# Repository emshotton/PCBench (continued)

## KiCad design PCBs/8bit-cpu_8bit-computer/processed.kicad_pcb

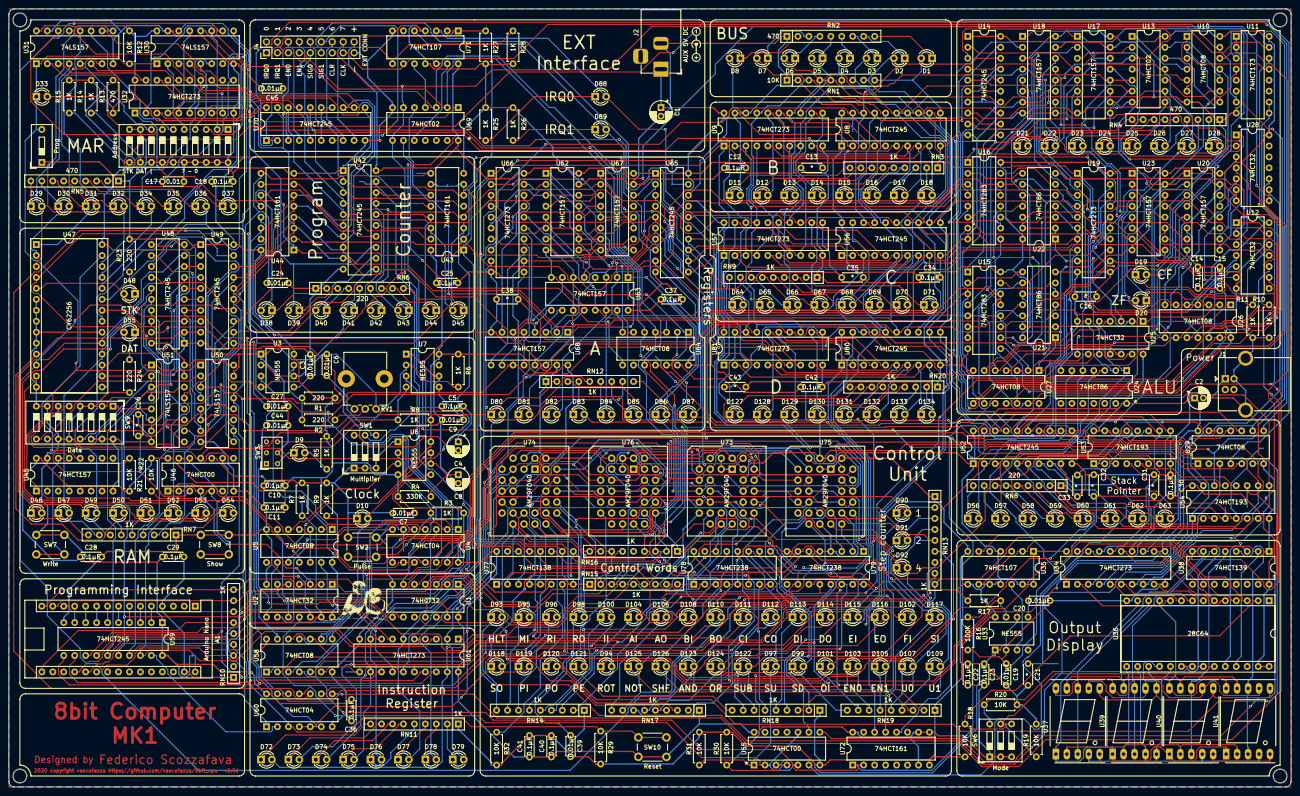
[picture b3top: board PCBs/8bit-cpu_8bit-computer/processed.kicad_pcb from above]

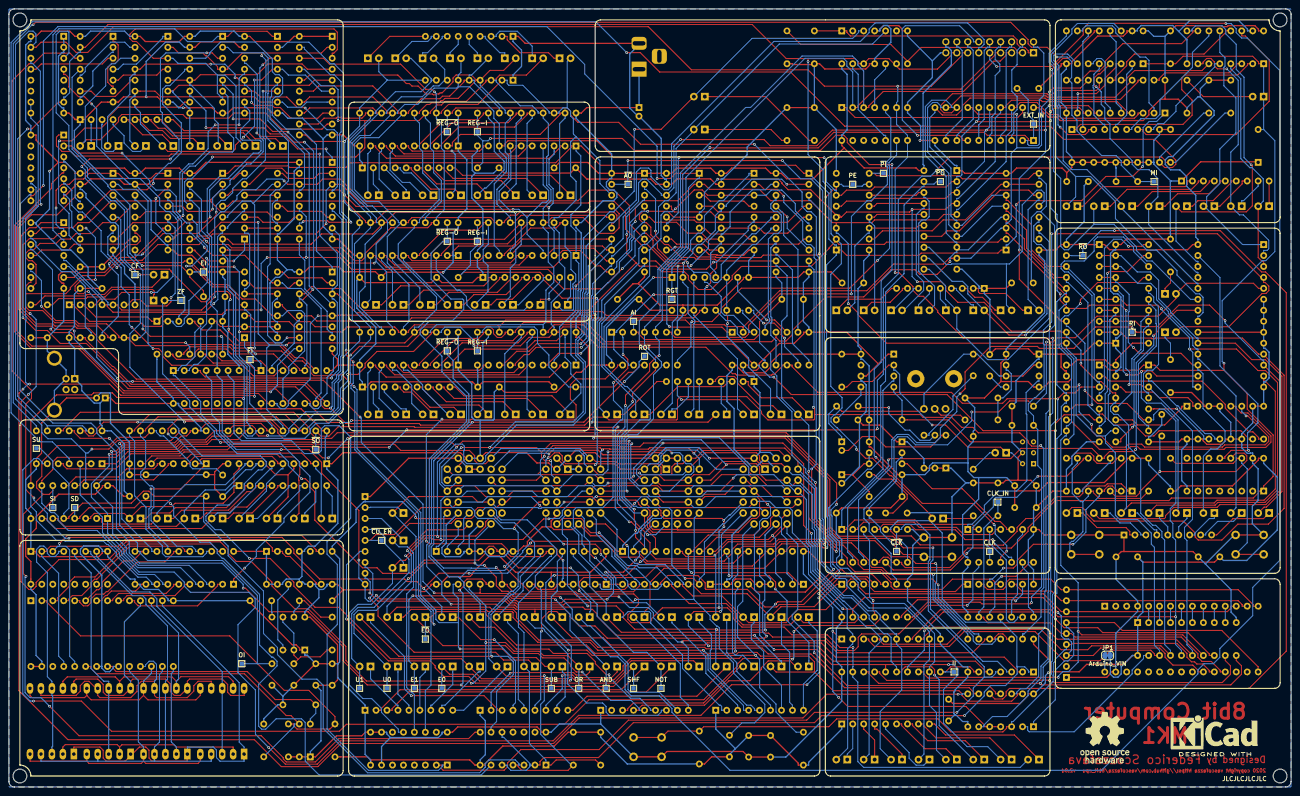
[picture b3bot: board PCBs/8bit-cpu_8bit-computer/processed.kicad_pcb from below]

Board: 2 copper layers, 297.2 x 180.3 mm, 377 parts (44 on the bottom side), 516 nets.

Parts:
A1: Arduino Nano; Arduino_Nano
C1, C2: 10µF; CP_Radial_D5.0mm_P2.00mm
C3, C6, C7, C9, C19, C20, C39, C45: 0.01µF; C_Disc_D4.3mm_W1.9mm_P5.00mm
C4, C8: 1µF; CP_Radial_D5.0mm_P2.00mm
C5, C10, C11, C12, C14, C15, C18, C22, C23, C25, C28, C29, C30, C34, C36, C37, C40, C41, C42: 0.1µF; C_Disc_D4.3mm_W1.9mm_P5.00mm
C13, C16, C21, C26, C31, C32, C33, C35, C38, C43: *; C_Disc_D4.3mm_W1.9mm_P5.00mm
C17: 0.01; C_Disc_D4.3mm_W1.9mm_P5.00mm
C24, C27, C44: 0.01µf; C_Disc_D4.3mm_W1.9mm_P5.00mm
D1, D2, D3, D4, D5, D6, D7, D8, D21, D22, D23, D24, D25, D26, D27, D28, D29, D30, D31, D32, D33, D34, D35, D36, D37: RED; LED_D3.0mm
D9, D11, D12, D13, D14, D15, D16, D17, D18, D46, D47, D49, D50, D51, D52, D53, D54, D64, D65, D66, D67, D68, D69, D70, D71, D80, D81, D82, D83, D84, D85, D86, D87, D127, D128, D129, D130, D131, D132, D133, D134: GREEN; LED_D3.0mm
D10, D72, D73, D74, D75, D76, D77, D78, D79, D93, D94, D95, D96, D97, D98, D99, D100, D101, D102, D103, D104, D105, D106, D107, D108, D109, D110, D111, D112, D113, D114, D115, D116, D117, D118, D119, D120, D121, D122, D123, D124, D125, D126: BLUE; LED_D3.0mm
D19, D20, D88, D89: WHITE; LED_D3.0mm
D38, D39, D40, D41, D42, D43, D44, D45, D48, D55, D56, D57, D58, D59, D60, D61, D62, D63, D90, D91, D92: YELLOW; LED_D3.0mm
G0: LOGO; parrot
G1: Symbol_Barrel_Polarity
G2: KiCad-Logo2_8mm_SilkScreen
G3: OSHW-Logo_11.4x12mm_SilkScreen
J1: USB_B-8bit-computer-rescue; USB_B_OST_USB-B1HSxx_Horizontal
J2: Barrel_Jack_Switch; BarrelJack_Horizontal
J4: EXT-CONN; PinHeader_2x09_P2.54mm_Vertical
JP1: Arduino_VIN; SolderJumper-2_P1.3mm_Bridged_RoundedPad1.0x1.5mm
MH0, MH1, MH2, MH3: MountingHole_3.2mm_M3
R1, R2, R23, R24: 220; R_Axial_DIN0207_L6.3mm_D2.5mm_P7.62mm_Horizontal
R3, R5, R6, R7, R8, R9, R10, R11, R14, R15, R17, R25, R26, R27, R28: 1K; R_Axial_DIN0207_L6.3mm_D2.5mm_P7.62mm_Horizontal
R4: 330K; R_Axial_DIN0207_L6.3mm_D2.5mm_P7.62mm_Horizontal
R12, R18, R19, R20, R21, R22, R29, R30, R31, R32: 10K; R_Axial_DIN0207_L6.3mm_D2.5mm_P7.62mm_Horizontal
R13: 470; R_Axial_DIN0207_L6.3mm_D2.5mm_P7.62mm_Horizontal
R16: 100K; R_Axial_DIN0207_L6.3mm_D2.5mm_P7.62mm_Horizontal
RN1: 10K; R_Array_SIP9
RN2, RN4, RN5: 470; R_Array_SIP9
RN3, RN7, RN9, RN10, RN11, RN12, RN13, RN14, RN15, RN16, RN17, RN18, RN19, RN20: 1K; R_Array_SIP9
RN6, RN8: 220; R_Array_SIP9
RV1: 1M; Potentiometer_Bourns_PTV09A-1_Single_Vertical
SW1: Multiplier; SW_DIP_SPSTx03_Slide_9.78x9.8mm_W7.62mm_P2.54mm
SW2: Pulse; SW_PUSH_6mm_H5mm
SW3: Manual; SW_NKK_GW12LJP
SW4: Prog; SW_DIP_SPSTx01_Slide_9.78x4.72mm_W7.62mm_P2.54mm
SW5: Address; SW_DIP_SPSTx10_Slide_9.78x27.58mm_W7.62mm_P2.54mm
SW6: Mode; SW_DIP_SPSTx03_Slide_9.78x9.8mm_W7.62mm_P2.54mm
SW7: Write; SW_PUSH_6mm_H5mm
SW8: Show; SW_PUSH_6mm_H5mm
SW9: Data; SW_DIP_SPSTx08_Slide_9.78x22.5mm_W7.62mm_P2.54mm
SW10: Reset; SW_PUSH_6mm_H5mm
TP1: CLK_IN; TestPoint_Pad_1.0x1.0mm
TP2: CLK; TestPoint_Pad_1.0x1.0mm
TP3: ~CLK; TestPoint_Pad_1.0x1.0mm
TP4, TP26, TP40: ~REG-O; TestPoint_Pad_1.0x1.0mm
TP5, TP27, TP41: REG-I; TestPoint_Pad_1.0x1.0mm
TP6: ~FI; TestPoint_Pad_1.0x1.0mm
TP7: ZF; TestPoint_Pad_1.0x1.0mm
TP8: CF; TestPoint_Pad_1.0x1.0mm
TP9: OR; TestPoint_Pad_1.0x1.0mm
TP10: AND; TestPoint_Pad_1.0x1.0mm
TP11: EI; TestPoint_Pad_1.0x1.0mm
TP12: ~EO; TestPoint_Pad_1.0x1.0mm
TP13: NOT; TestPoint_Pad_1.0x1.0mm
TP14: SUB; TestPoint_Pad_1.0x1.0mm
TP15: MI; TestPoint_Pad_1.0x1.0mm
TP16: OI; TestPoint_Pad_1.0x1.0mm
TP17: ~PO; TestPoint_Pad_1.0x1.0mm
TP18: PE; TestPoint_Pad_1.0x1.0mm
TP19: ~PI; TestPoint_Pad_1.0x1.0mm
TP20: ~RO; TestPoint_Pad_1.0x1.0mm
TP21: RI; TestPoint_Pad_1.0x1.0mm
TP22: ~SO; TestPoint_Pad_1.0x1.0mm
TP23: SU; TestPoint_Pad_1.0x1.0mm
TP24: SD; TestPoint_Pad_1.0x1.0mm
TP25: SI; TestPoint_Pad_1.0x1.0mm
TP28: II; TestPoint_Pad_1.0x1.0mm
TP29: AI; TestPoint_Pad_1.0x1.0mm
TP30: ~AO; TestPoint_Pad_1.0x1.0mm
TP31: RGT; TestPoint_Pad_1.0x1.0mm
TP32: ROT; TestPoint_Pad_1.0x1.0mm
TP33: SHF; TestPoint_Pad_1.0x1.0mm
TP34: E0; TestPoint_Pad_1.0x1.0mm
TP35: EXT_IN; TestPoint_Pad_1.0x1.0mm
TP36: E1; TestPoint_Pad_1.0x1.0mm
TP37: U0; TestPoint_Pad_1.0x1.0mm
TP38: U1; TestPoint_Pad_1.0x1.0mm
TP39: ~CU_EN; TestPoint_Pad_1.0x1.0mm
U1, U2, U12, U25, U28: 74HCT32; DIP-14_W7.62mm
U3, U6, U7, U33: NE555; DIP-8_W7.62mm
U4, U60: 74HCT04; DIP-14_W7.62mm
U5, U10, U26, U27, U29, U58, U64: 74HCT08; DIP-14_W7.62mm
U8, U14, U42, U48, U49, U52, U56, U59, U65, U70, U80: 74HCT245; DIP-20_W7.62mm
U9, U19, U32, U34, U57, U61, U66, U81: 74HCT273; DIP-20_W7.62mm
U11: 74HCT173; DIP-16_W7.62mm
U13, U69: 74HCT02; DIP-14_W7.62mm
U15, U16: 74HCT283; DIP-16_W7.62mm
U17, U18, U20, U23, U45, U62, U63, U67, U68: 74HCT157; DIP-16_W7.62mm
U21, U22, U24: 74HCT86; DIP-14_W7.62mm
U30, U31, U50, U51: 74LS157; DIP-16_W7.62mm
U35, U71: 74HCT107; DIP-14_W7.62mm
U36: 28C64; DIP-28_W15.24mm_Socket
U37, U39, U40, U41: 7SEGMENT_CC; 7SegmentLED_LTS6760_LTS6780
U38: 74HCT139; DIP-16_W7.62mm
U43, U44, U72: 74HCT161; DIP-16_W7.62mm
U46, U55: 74HCT00; DIP-14_W7.62mm
U47: CY62256; DIP-28_W15.24mm_Socket
U53, U54: 74HCT193; DIP-16_W7.62mm
U73, U74, U75, U76: AM29F040; PLCC-32_THT-Socket
U77: 74HCT138; DIP-16_W7.62mm
U78, U79: 74HCT238; DIP-16_W7.62mm

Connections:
/A register/AI: D104.2, U64.2, U78.14
/A register/RGT: TP31.1, U62.1, U63.1, U76.18
/A register/ROT: D94.2, TP32.1, U28.10, U58.10, U58.12, U79.10
/A register/SFT: D126.2, TP33.1, U28.9, U79.11
/A register/~AO: D106.1, TP30.1, U65.19, U77.14
/ALU/AND: D123.2, TP10.1, U12.1, U79.12
/ALU/CF: D19.2, TP8.1, U11.3, U73.25, U74.25, U75.25, U76.25
/ALU/EI: D115.2, U10.12, U78.9
/ALU/NOT: D125.2, TP13.1, U24.1, U25.5, U79.7
/ALU/OR: D124.2, TP9.1, U12.2, U20.1, U23.1, U79.13
/ALU/SUB: D122.2, TP14.1, U25.4, U79.14
/ALU/ZF: D20.2, TP7.1, U11.4, U73.4, U74.4, U75.4, U76.4
/ALU/~EO: D116.1, TP12.1, U14.19, U77.7
/ALU/~FI: TP6.1, U11.9, U11.10, U60.8
/A_0: D87.2, U12.12, U16.5, U26.13, U58.13, U62.5, U65.9, U66.9
/A_1: D86.2, U12.9, U16.3, U26.10, U62.3, U62.14, U65.8, U66.6
/A_2: D85.2, U12.4, U16.14, U26.5, U62.6, U62.11, U65.7, U66.5
/A_3: D84.2, U16.12, U25.1, U26.2, U62.13, U63.2, U65.6, U66.2
/A_4: D83.2, U15.5, U27.13, U28.4, U62.10, U63.5, U65.5, U66.19
/A_5: D82.2, U15.3, U27.10, U28.1, U63.3, U63.14, U65.4, U66.16
/A_6: D81.2, U15.14, U25.12, U27.5, U63.6, U63.11, U65.3, U66.15
/A_7: D80.2, U15.12, U25.9, U27.2, U58.9, U63.13, U65.2, U66.12
/B register/OUT_0: D18.2, U8.9, U9.2
/B register/OUT_1: D17.2, U8.8, U9.5
/B register/OUT_2: D16.2, U8.7, U9.6
/B register/OUT_3: D15.2, U8.6, U9.9
/B register/OUT_4: D14.2, U8.5, U9.12
/B register/OUT_5: D13.2, U8.4, U9.15
/B register/OUT_6: D12.2, U8.3, U9.16
/B register/OUT_7: D11.2, U8.2, U9.19
/BUS_0: D1.2, RN1.9, U8.11, U9.3, U14.11, U19.3, U32.3, U34.3, U42.5, U43.3, U49.11, U51.10, U52.11, U54.15, U56.11, U57.3, U59.18, U61.3, U65.11, U67.2, U70.18, U80.11, U81.3
/BUS_1: D2.2, RN1.8, U8.12, U9.4, U14.12, U19.4, U32.4, U34.4, U42.4, U43.4, U49.12, U51.13, U52.12, U54.1, U56.12, U57.4, U59.17, U61.4, U65.12, U67.5, U70.17, U80.12, U81.4
/BUS_2: D3.2, RN1.7, U8.13, U9.7, U14.13, U19.7, U32.7, U34.7, U42.3, U43.5, U49.13, U51.6, U52.13, U54.10, U56.13, U57.7, U59.16, U61.7, U65.13, U67.14, U70.16, U80.13, U81.7
/BUS_3: D4.2, RN1.6, U8.14, U9.8, U14.14, U19.8, U32.8, U34.8, U42.2, U43.6, U49.14, U51.3, U52.14, U54.9, U56.14, U57.8, U59.15, U61.8, U65.14, U67.11, U70.15, U80.14, U81.8
/BUS_4: D5.2, RN1.5, U8.15, U9.13, U14.15, U19.13, U32.13, U34.13, U42.9, U44.3, U49.15, U50.10, U52.15, U53.15, U56.15, U57.13, U59.14, U61.13, U65.15, U68.2, U70.14, U80.15, U81.13
/BUS_5: D6.2, RN1.4, U8.16, U9.14, U14.16, U19.14, U32.14, U34.14, U42.8, U44.4, U49.16, U50.13, U52.16, U53.1, U56.16, U57.14, U59.13, U61.14, U65.16, U68.5, U70.13, U80.16, U81.14
/BUS_6: D7.2, RN1.3, U8.17, U9.17, U14.17, U19.17, U32.17, U34.17, U42.7, U44.5, U49.17, U50.6, U52.17, U53.10, U56.17, U57.17, U59.12, U61.17, U65.17, U68.14, U70.12, U80.17, U81.17
/BUS_7: D8.2, RN1.2, U8.18, U9.18, U14.18, U19.18, U32.18, U34.18, U42.6, U44.6, U49.18, U50.3, U52.18, U53.9, U56.18, U57.18, U59.11, U61.18, U65.18, U68.11, U70.11, U80.18, U81.18
/C register/OUT_0: D71.2, U56.9, U57.2
/C register/OUT_1: D70.2, U56.8, U57.5
/C register/OUT_2: D69.2, U56.7, U57.6
/C register/OUT_3: D68.2, U56.6, U57.9
/C register/OUT_4: D67.2, U56.5, U57.12
/C register/OUT_5: D66.2, U56.4, U57.15
/C register/OUT_6: D65.2, U56.3, U57.16
/C register/OUT_7: D64.2, U56.2, U57.19
/CLK: D10.2, J4.15, TP2.1, U2.11, U4.5, U5.12, U10.13, U11.7, U29.9, U29.13, U43.2, U44.2, U46.1, U55.2, U55.5, U55.10, U58.1, U64.1, U64.12, U71.9, U71.12
/CLR: J4.13, U11.15, U53.14, U54.14, U60.6, U69.6, U69.8
/Clock/CLK_IN: A1.19, R7.1, RN10.5, TP1.1, U2.13
/Clock/HLT: U1.11, U4.3
/Control logic/BI: D108.2, U5.13, U78.13
/Control logic/CI: D111.2, U58.2, U78.12
/Control logic/DI: D113.2, U64.13, U78.11
/Control logic/E0: D103.2, J4.5, RN16.4, TP34.1, U64.10, U69.3, U76.21
/Control logic/E1: D105.2, J4.7, RN16.3, TP36.1, U64.5, U69.2, U76.20
/Control logic/EXT_I: C45.1, RN15.2, TP35.1, U64.4, U64.9, U70.1, U74.19
/Control logic/HL: RN16.2, U2.4, U76.19
/Control logic/HLT: D93.2, RN15.5, U1.12, U73.21
/Control logic/II: D100.2, U58.5, U74.21
/Control logic/IRQ0: D88.2, U71.3, U73.28, U74.28, U75.28, U76.28
/Control logic/IRQ1: D89.2, U71.5, U73.29, U74.29, U75.29, U76.29
/Control logic/MI: D95.2, RN15.3, U1.1, U73.14
/Control logic/OI: D101.2, R32.1, U29.12, U74.20
/Control logic/PE: D121.2, TP18.1, U43.7, U43.10, U73.19
/Control logic/RI: D96.2, RN15.4, U2.1, U73.13
/Control logic/SD: D99.2, R30.1, U55.4, U75.15
/Control logic/SI: D117.2, U55.9, U78.10
/Control logic/STK: RN15.6, U1.5, U73.20
/Control logic/SU: D97.2, R31.1, U55.1, U75.17
/Control logic/U0: D107.2, J4.9, TP37.1, U75.14
/Control logic/U1: D109.2, J4.11, TP38.1, U75.13
/Control logic/~BO: D110.1, TP4.1, U8.19, U77.13
/Control logic/~CO: D112.1, TP26.1, U56.19, U77.12
/Control logic/~DO: D114.1, TP40.1, U77.11, U80.19
/Control logic/~PI: C24.1, TP19.1, U43.9, U44.9, U60.12
/Control logic/~PO: D120.1, TP17.1, U42.19, U77.10
/Control logic/~RO: TP20.1, U49.19, U60.10
/Control logic/~SO: D118.1, TP22.1, U52.19, U77.9
/D register/OUT_0: D134.2, U80.9, U81.2
/D register/OUT_1: D133.2, U80.8, U81.5
/D register/OUT_2: D132.2, U80.7, U81.6
/D register/OUT_3: D131.2, U80.6, U81.9
/D register/OUT_4: D130.2, U80.5, U81.12
/D register/OUT_5: D129.2, U80.4, U81.15
/D register/OUT_6: D128.2, U80.3, U81.16
/D register/OUT_7: D127.2, U80.2, U81.19
/IR_0: D79.2, U61.2, U73.9, U74.9, U75.9, U76.9
/IR_1: D78.2, U61.5, U73.8, U74.8, U75.8, U76.8
/IR_2: D77.2, U61.6, U73.7, U74.7, U75.7, U76.7
/IR_3: D76.2, U61.9, U73.6, U74.6, U75.6, U76.6
/IR_4: D75.2, U61.12, U73.5, U74.5, U75.5, U76.5
/IR_5: D74.2, U61.15, U73.27, U74.27, U75.27, U76.27
/IR_6: D73.2, U61.16, U73.26, U74.26, U75.26, U76.26
/IR_7: D72.2, U61.19, U73.23, U74.23, U75.23, U76.23
/MAR/A0: D37.2, U30.9, U47.21
/MAR/A1: D36.2, U30.12, U47.23
/MAR/A2: D35.2, U30.7, U47.24
/MAR/A3: D34.2, U30.4, U47.25
/MAR/A4: D32.2, U31.9, U47.26
/MAR/A5: D31.2, U31.12, U47.1
/MAR/A6: D30.2, U31.7, U47.2
/MAR/A7: D29.2, U31.4, U47.3
/MAR/HL: U1.10, U29.6
/MAR/MI: U1.3, U29.10
/MAR/STK: U1.4, U29.3
/MAR/~PROG: D33.1, R12.2, SW4.2, U4.9, U4.11, U30.1, U31.1, U45.1, U50.1, U51.1
/PC Interface/CLR: A1.20, R29.1, RN10.4, SW10.1, U60.3
/PC Interface/CU_DIS: A1.21, RN10.3, RN13.5, TP39.1, U1.13, U73.24, U74.24, U75.24, U76.24
/PC Interface/HL: A1.14, RN10.8, U2.5
/PC Interface/MI: A1.13, RN10.7, U1.2
/PC Interface/RI: A1.15, RN10.9, U2.2
/RAM/HL: C44.1, D55.2, U1.8, U47.4
/RAM/RI: U2.3, U46.2, U46.4
/RAM/STK: C27.1, D48.2, U1.6, U47.5
/~CLK: TP3.1, U4.6, U58.4, U72.2
/~CLR: U9.1, U19.1, U24.5, U32.1, U34.1, U43.1, U44.1, U57.1, U60.4, U60.5, U61.1, U66.1, U81.1
GND: A1.4, A1.29, C1.2, C2.2, C3.2, C7.2, C8.2, C9.2, C10.2, C11.2, C12.2, C13.2, C14.2, C15.2, C16.2, C17.2, C18.2, C19.2, C20.2, C21.2, C22.2, C23.2, C24.2, C25.2, C26.2, C27.2, C28.2, C29.2, C30.2, C31.2, C32.2, C33.2, C34.2, C35.2, C36.2, C37.2, C38.2, C39.2, C40.2, C41.2, C42.2, C43.2, C44.2, C45.2, J1.4, J1.5, J2.2, J4.17, R7.2, R9.2, R10.1, R11.1, R18.2, R19.2, R20.2, R23.2, R24.2, R25.1, R26.1, R27.2, R28.2, R29.2, R30.2, R31.2, R32.2, RN1.1, RN2.1, RN3.1, RN4.1, RN5.1, RN6.1, RN7.1, RN8.1, RN9.1, RN10.1, RN11.1, RN12.1, RN13.1, RN14.1, RN15.1, RN16.1, RN18.1, RN19.1, RN20.1, SW1.1, SW1.2, SW1.3, SW2.1, SW3.5, SW4.1, SW5.9, SW5.10, SW5.13, SW5.14, SW5.15, SW5.16, SW5.17, SW5.18, SW5.19, SW5.20, SW7.1, SW8.1, SW9.3, SW9.4, SW9.7, SW9.8, SW9.11, SW9.12, SW9.15, SW9.16, U1.7, U2.7, U3.1, U4.7, U5.7, U6.1, U7.1, U7.6, U8.10, U9.10, U10.7, U11.1, U11.2, U11.8, U12.7, U13.7, U14.10, U15.8, U16.8, U17.8, U17.15, U18.8, U18.15, U19.10, U20.8, U20.15, U21.7, U22.7, U23.8, U23.15, U24.7, U25.7, U26.7, U27.7, U28.7, U29.7, U30.8, U30.15, U31.8, U31.15, U32.10, U33.1, U34.10, U35.7, U36.14, U36.20, U36.22, U38.1, U38.8, U42.1, U42.10, U43.8, U44.8, U45.8, U45.15, U46.7, U47.6, U47.7, U47.8, U47.9, U47.10, U47.14, U47.20, U48.1, U48.10, U49.10, U50.8, U50.15, U51.8, U51.15, U52.10, U53.8, U54.8, U55.7, U56.10, U57.10, U58.7, U59.10, U60.7, U61.10, U62.8, U62.15, U63.8, U63.15, U64.7, U65.10, U66.10, U67.8, U67.15, U68.8, U68.15, U69.7, U70.10, U71.4, U71.7, U71.11, U72.8, U73.1, U73.2, U73.3, U73.16, U73.22, U73.30, U74.1, U74.2, U74.16, U74.22, U74.30, U75.1, U75.3, U75.16, U75.22, U75.30, U76.1, U76.16, U76.22, U76.30, U77.4, U77.5, U77.8, U78.4, U78.5, U78.8, U79.4, U79.5, U79.8, U80.10, U81.10
unnamed: A1.5, U59.2
unnamed: A1.6, U59.3
unnamed: A1.7, U59.4
unnamed: A1.8, U59.5
unnamed: A1.9, U59.6
unnamed: A1.10, U59.7
unnamed: A1.11, U59.8
unnamed: A1.12, U59.9
unnamed: A1.16, RN10.6, U60.1
unnamed: A1.30, JP1.1
unnamed: C3.1, U3.5
unnamed: C4.1, C5.1, C6.1, RV1.1, U3.2, U3.6
unnamed: C4.2, SW1.6
unnamed: C5.2, SW1.5
unnamed: C6.2, SW1.4
unnamed: C7.1, U6.5
unnamed: C8.1, R4.2, U6.6, U6.7
unnamed: C9.1, U7.5
unnamed: C13.1, TP5.1, U5.11, U9.11
unnamed: C16.1, TP11.1, U10.11, U19.11
unnamed: C17.1, TP15.1, U29.8, U32.11
unnamed: C19.1, R16.2, U33.2, U33.6
unnamed: C20.1, U33.5
unnamed: C21.1, TP16.1, U29.11, U34.11
unnamed: C26.1, U45.13, U46.3
unnamed: C31.1, TP24.1, U54.4, U55.6
unnamed: C32.1, TP23.1, U54.5, U55.3
unnamed: C33.1, TP25.1, U53.11, U54.11, U55.8
unnamed: C35.1, TP27.1, U57.11, U58.3
unnamed: C38.1, TP29.1, U64.3, U66.11
unnamed: C39.1, RN13.9, U24.4, U76.13
unnamed: C43.1, TP41.1, U64.11, U81.11
unnamed: D1.1, RN2.9
unnamed: D2.1, RN2.8
unnamed: D3.1, RN2.7
unnamed: D4.1, RN2.6
unnamed: D5.1, RN2.5
unnamed: D6.1, RN2.4
unnamed: D7.1, RN2.3
unnamed: D8.1, RN2.2
unnamed: D9.1, R6.2, SW3.4, U7.2
unnamed: D9.2, R5.1
unnamed: D10.1, R9.1
unnamed: D11.1, RN3.9
unnamed: D12.1, RN3.8
unnamed: D13.1, RN3.7
unnamed: D14.1, RN3.6
unnamed: D15.1, RN3.5
unnamed: D16.1, RN3.4
unnamed: D17.1, RN3.3
unnamed: D18.1, RN3.2
unnamed: D19.1, R10.2
unnamed: D20.1, R11.2
unnamed: D21.1, RN4.9
unnamed: D21.2, U13.2, U14.2, U17.4
unnamed: D22.1, RN4.8
unnamed: D22.2, U13.3, U14.3, U17.7
unnamed: D23.1, RN4.7
unnamed: D23.2, U13.5, U14.4, U17.12
unnamed: D24.1, RN4.6
unnamed: D24.2, U13.6, U14.5, U17.9
unnamed: D25.1, RN4.5
unnamed: D25.2, U13.8, U14.6, U18.4
unnamed: D26.1, RN4.4
unnamed: D26.2, U13.9, U14.7, U18.7
unnamed: D27.1, RN4.3
unnamed: D27.2, U13.11, U14.8, U18.12
unnamed: D28.1, RN4.2
unnamed: D28.2, U13.12, U14.9, U18.9
unnamed: D29.1, RN5.9
unnamed: D30.1, RN5.8
unnamed: D31.1, RN5.7
unnamed: D32.1, RN5.6
unnamed: D33.2, R13.1
unnamed: D34.1, RN5.5
unnamed: D35.1, RN5.4
unnamed: D36.1, RN5.3
unnamed: D37.1, RN5.2
unnamed: D38.1, RN6.2
unnamed: D38.2, U42.14, U44.11
unnamed: D39.1, RN6.3
unnamed: D39.2, U42.13, U44.12
unnamed: D40.1, RN6.4
unnamed: D40.2, U42.12, U44.13
unnamed: D41.1, RN6.5
unnamed: D41.2, U42.11, U44.14
unnamed: D42.1, RN6.6
unnamed: D42.2, U42.18, U43.11
unnamed: D43.1, RN6.7
unnamed: D43.2, U42.17, U43.12
unnamed: D44.1, RN6.8
unnamed: D44.2, U42.16, U43.13
unnamed: D45.1, RN6.9
unnamed: D45.2, U42.15, U43.14
unnamed: D46.1, RN7.9
unnamed: D46.2, U47.19, U48.9, U49.2
unnamed: D47.1, RN7.8
unnamed: D47.2, U47.18, U48.8, U49.3
unnamed: D48.1, R23.1
unnamed: D49.1, RN7.7
unnamed: D49.2, U47.17, U48.7, U49.4
unnamed: D50.1, RN7.6
unnamed: D50.2, U47.16, U48.6, U49.5
unnamed: D51.1, RN7.5
unnamed: D51.2, U47.15, U48.5, U49.6
unnamed: D52.1, RN7.4
unnamed: D52.2, U47.13, U48.4, U49.7
unnamed: D53.1, RN7.3
unnamed: D53.2, U47.12, U48.3, U49.8
unnamed: D54.1, RN7.2
unnamed: D54.2, U47.11, U48.2, U49.9
unnamed: D55.1, R24.1
unnamed: D56.1, RN8.9
unnamed: D56.2, U52.2, U53.7
unnamed: D57.1, RN8.8
unnamed: D57.2, U52.3, U53.6
unnamed: D58.1, RN8.7
unnamed: D58.2, U52.4, U53.2
unnamed: D59.1, RN8.6
unnamed: D59.2, U52.5, U53.3
unnamed: D60.1, RN8.5
unnamed: D60.2, U52.6, U54.7
unnamed: D61.1, RN8.4
unnamed: D61.2, U52.7, U54.6
unnamed: D62.1, RN8.3
unnamed: D62.2, U52.8, U54.2
unnamed: D63.1, RN8.2
unnamed: D63.2, U52.9, U54.3
unnamed: D64.1, RN9.9
unnamed: D65.1, RN9.8
unnamed: D66.1, RN9.7
unnamed: D67.1, RN9.6
unnamed: D68.1, RN9.5
unnamed: D69.1, RN9.4
unnamed: D70.1, RN9.3
unnamed: D71.1, RN9.2
unnamed: D72.1, RN11.9
unnamed: D73.1, RN11.8
unnamed: D74.1, RN11.7
unnamed: D75.1, RN11.6
unnamed: D76.1, RN11.5
unnamed: D77.1, RN11.4
unnamed: D78.1, RN11.3
unnamed: D79.1, RN11.2
unnamed: D80.1, RN12.2
unnamed: D81.1, RN12.5
unnamed: D82.1, RN12.8
unnamed: D83.1, RN12.4
unnamed: D84.1, RN12.6
unnamed: D85.1, RN12.7
unnamed: D86.1, RN12.3
unnamed: D87.1, RN12.9
unnamed: D88.1, R25.2
unnamed: D89.1, R26.2
unnamed: D90.1, RN13.2
unnamed: D90.2, U72.14, U73.12, U74.12, U75.12, U76.12
unnamed: D91.1, RN13.3
unnamed: D91.2, U72.13, U73.11, U74.11, U75.11, U76.11
unnamed: D92.1, RN13.4
unnamed: D92.2, U72.12, U73.10, U74.10, U75.10, U76.10
unnamed: D93.1, RN14.9
unnamed: D94.1, RN13.6
unnamed: D95.1, RN14.8
unnamed: D96.1, RN14.7
unnamed: D97.1, RN13.7
unnamed: D98.1, RN14.6
unnamed: D98.2, RN16.6, U60.11, U74.14
unnamed: D99.1, RN19.9
unnamed: D100.1, RN14.5
unnamed: D101.1, RN19.8
unnamed: D102.1, RN14.4
unnamed: D102.2, U60.9, U75.18
unnamed: D103.1, RN19.7
unnamed: D104.1, RN14.3
unnamed: D105.1, RN19.6
unnamed: D106.2, RN17.9
unnamed: D107.1, RN19.5
unnamed: D108.1, RN14.2
unnamed: D109.1, RN19.4
unnamed: D110.2, RN17.8
unnamed: D111.1, RN18.6
unnamed: D112.2, RN17.7
unnamed: D113.1, RN18.5
unnamed: D114.2, RN17.6
unnamed: D115.1, RN18.4
unnamed: D116.2, RN17.5
unnamed: D117.1, RN18.3
unnamed: D118.2, RN17.4
unnamed: D119.1, RN13.8
unnamed: D119.2, U60.13, U78.7
unnamed: D120.2, RN17.3
unnamed: D121.1, RN18.9
unnamed: D122.1, RN18.8
unnamed: D123.1, RN18.7
unnamed: D124.1, RN18.2
unnamed: D125.1, RN19.3
unnamed: D126.1, RN19.2
unnamed: D127.1, RN20.9
unnamed: D128.1, RN20.8
unnamed: D129.1, RN20.7
unnamed: D130.1, RN20.6
unnamed: D131.1, RN20.5
unnamed: D132.1, RN20.4
unnamed: D133.1, RN20.3
unnamed: D134.1, RN20.2
unnamed: J4.1, R27.1, U71.1
unnamed: J4.2, U70.2
unnamed: J4.3, R28.1, U71.8
unnamed: J4.4, U70.3
unnamed: J4.6, U70.4
unnamed: J4.8, U70.5
unnamed: J4.10, U70.6
unnamed: J4.12, U70.7
unnamed: J4.14, U70.8
unnamed: J4.16, U70.9
unnamed: R1.2, R2.2, U3.7
unnamed: R2.1, RV1.2
unnamed: R3.2, SW2.2, U6.2
unnamed: R8.2, SW3.6, U7.4
unnamed: R14.2, SW5.12, U29.4
unnamed: R15.2, SW5.11, U29.1
unnamed: R16.1, R17.2, U33.7
unnamed: R18.1, SW6.4, U36.2
unnamed: R19.1, SW6.5, U36.23
unnamed: R20.1, SW6.6, U36.21
unnamed: R21.1, SW7.2, U45.14
unnamed: R22.1, SW8.2, U46.5, U46.9
unnamed: RN15.7, U73.15, U78.3
unnamed: RN15.8, U73.17, U78.2
unnamed: RN15.9, U73.18, U78.1
unnamed: RN16.7, U74.18, U77.1
unnamed: RN16.8, U74.17, U77.2
unnamed: RN16.9, U74.15, U77.3
unnamed: SW5.1, U31.2
unnamed: SW5.2, U30.11
unnamed: SW5.3, U30.14
unnamed: SW5.4, U30.5
unnamed: SW5.5, U30.2
unnamed: SW5.6, U31.11
unnamed: SW5.7, U31.14
unnamed: SW5.8, U31.5
unnamed: SW9.1, U51.11
unnamed: SW9.2, U51.14
unnamed: SW9.5, U50.11
unnamed: SW9.6, U50.14
unnamed: SW9.9, U50.2
unnamed: SW9.10, U50.5
unnamed: SW9.13, U51.2
unnamed: SW9.14, U51.5
unnamed: TP21.1, U4.12, U48.19
unnamed: TP28.1, U58.6, U61.11
unnamed: U1.9, U2.6
unnamed: U2.8, U5.9
unnamed: U2.9, U5.3
unnamed: U2.10, U5.6
unnamed: U2.12, U5.8
unnamed: U3.3, U5.1
unnamed: U4.1, U5.2, U7.3
unnamed: U4.2, U5.4
unnamed: U4.4, U5.10
unnamed: U4.10, U46.10
unnamed: U4.13, U46.11, U47.22
unnamed: U5.5, U6.3
unnamed: U10.1, U10.6
unnamed: U10.2, U10.8
unnamed: U10.3, U11.13
unnamed: U10.4, U13.1
unnamed: U10.5, U13.4
unnamed: U10.9, U13.10
unnamed: U10.10, U13.13
unnamed: U11.14, U15.9
unnamed: U12.3, U17.1, U18.1
unnamed: U12.5, U19.6, U22.4, U26.4
unnamed: U12.6, U23.6
unnamed: U12.8, U23.13
unnamed: U12.10, U19.5, U22.9, U26.9
unnamed: U12.11, U23.10
unnamed: U12.13, U19.2, U22.12, U26.12
unnamed: U15.1, U17.14
unnamed: U15.2, U21.8
unnamed: U15.4, U17.11
unnamed: U15.6, U21.11
unnamed: U15.7, U16.9
unnamed: U15.10, U17.2
unnamed: U15.11, U21.3
unnamed: U15.13, U17.5
unnamed: U15.15, U21.6
unnamed: U16.1, U18.14
unnamed: U16.2, U22.8
unnamed: U16.4, U18.11
unnamed: U16.6, U22.11
unnamed: U16.7, U24.3
unnamed: U16.10, U18.2
unnamed: U16.11, U22.3
unnamed: U16.13, U18.5
unnamed: U16.15, U22.6
unnamed: U17.3, U20.4
unnamed: U17.6, U20.7
unnamed: U17.10, U20.9
unnamed: U17.13, U20.12
unnamed: U18.3, U23.4
unnamed: U18.6, U23.7
unnamed: U18.10, U23.9
unnamed: U18.13, U23.12
unnamed: U19.9, U22.1, U25.2, U26.1
unnamed: U19.12, U21.12, U27.12, U28.5
unnamed: U19.15, U21.9, U27.9, U28.2
unnamed: U19.16, U21.4, U25.13, U27.4
unnamed: U19.19, U21.1, U25.10, U27.1
unnamed: U20.2, U27.3
unnamed: U20.3, U25.8
unnamed: U20.5, U27.6
unnamed: U20.6, U25.11
unnamed: U20.10, U28.6
unnamed: U20.11, U27.11
unnamed: U20.13, U28.3
unnamed: U20.14, U27.8
unnamed: U21.2, U21.5, U21.10, U21.13, U22.2, U22.5, U22.10, U22.13, U24.2, U25.6
unnamed: U23.2, U26.3
unnamed: U23.3, U25.3
unnamed: U23.5, U26.6
unnamed: U23.11, U26.11
unnamed: U23.14, U26.8
unnamed: U24.6, U72.1
unnamed: U28.8, U67.1, U68.1
unnamed: U4.8, U29.2, U29.5
unnamed: U30.3, U32.9
unnamed: U30.6, U32.6
unnamed: U30.10, U32.2
unnamed: U30.13, U32.5
unnamed: U31.3, U32.19
unnamed: U31.6, U32.16
unnamed: U31.10, U32.12
unnamed: U31.13, U32.15
unnamed: U33.3, U35.12
unnamed: U34.2, U36.10
unnamed: U34.5, U36.9
unnamed: U34.6, U36.8
unnamed: U34.9, U36.7
unnamed: U34.12, U36.6
unnamed: U34.15, U36.5
unnamed: U34.16, U36.4
unnamed: U34.19, U36.3
unnamed: U35.2, U35.9, U36.25, U38.2
unnamed: U35.6, U36.24, U38.3
unnamed: U36.11, U37.10, U39.10, U40.10, U41.10
unnamed: U36.12, U37.9, U39.9, U40.9, U41.9
unnamed: U36.13, U37.1, U39.1, U40.1, U41.1
unnamed: U36.15, U37.2, U39.2, U40.2, U41.2
unnamed: U36.16, U37.4, U39.4, U40.4, U41.4
unnamed: U36.17, U37.6, U39.6, U40.6, U41.6
unnamed: U36.18, U37.7, U39.7, U40.7, U41.7
unnamed: U36.19, U37.5, U39.5, U40.5, U41.5
unnamed: U37.3, U37.8, U38.7
unnamed: U38.4, U41.3, U41.8
unnamed: U38.5, U40.3, U40.8
unnamed: U38.6, U39.3, U39.8
unnamed: U43.15, U44.7, U44.10
unnamed: U45.12, U47.27
unnamed: U46.6, U46.12
unnamed: U46.8, U46.13
unnamed: U48.11, U50.4
unnamed: U48.12, U50.7
unnamed: U48.13, U50.12
unnamed: U48.14, U50.9
unnamed: U48.15, U51.4
unnamed: U48.16, U51.7
unnamed: U48.17, U51.12
unnamed: U48.18, U51.9
unnamed: U53.4, U54.13
unnamed: U53.5, U54.12
unnamed: U58.8, U62.2
unnamed: U58.11, U63.10
unnamed: U59.19, U60.2
unnamed: U62.4, U67.3
unnamed: U62.7, U67.6
unnamed: U62.9, U67.10
unnamed: U62.12, U67.13
unnamed: U63.4, U68.3
unnamed: U63.7, U68.6
unnamed: U63.9, U68.10
unnamed: U63.12, U68.13
unnamed: U64.6, U69.5
unnamed: U64.8, U69.9
unnamed: U66.3, U67.9
unnamed: U66.4, U67.12
unnamed: U66.7, U67.7
unnamed: U66.8, U67.4
unnamed: U66.13, U68.9
unnamed: U66.14, U68.12
unnamed: U66.17, U68.7
unnamed: U66.18, U68.4
unnamed: U69.1, U70.19
unnamed: U69.4, U71.10
unnamed: U69.10, U71.13
unnamed: U75.19, U79.3
unnamed: U75.20, U79.2
unnamed: U75.21, U79.1
VCC: C1.1, C2.1, C10.1, C11.1, C12.1, C14.1, C15.1, C18.1, C22.1, C23.1, C25.1, C28.1, C29.1, C30.1, C34.1, C36.1, C37.1, C40.1, C41.1, C42.1, J1.1, J2.1, J4.18, JP1.2, R1.1, R3.1, R4.1, R5.2, R6.1, R8.1, R12.1, R13.2, R14.1, R15.1, R17.1, R21.2, R22.2, RN17.1, SW6.1, SW6.2, SW6.3, SW10.2, U1.14, U2.14, U3.4, U3.8, U4.14, U5.14, U6.4, U6.8, U7.8, U8.1, U8.20, U9.20, U10.14, U11.16, U12.14, U13.14, U14.1, U14.20, U15.16, U16.16, U17.16, U18.16, U19.20, U20.16, U21.14, U22.14, U23.16, U24.14, U25.14, U26.14, U27.14, U28.14, U29.14, U30.16, U31.16, U32.20, U33.8, U34.20, U35.1, U35.4, U35.8, U35.10, U35.11, U35.13, U35.14, U36.27, U36.28, U38.16, U42.20, U43.16, U44.16, U45.16, U46.14, U47.28, U48.20, U49.1, U49.20, U50.16, U51.16, U52.1, U52.20, U53.16, U54.16, U55.14, U56.1, U56.20, U57.20, U58.14, U59.1, U59.20, U60.14, U61.20, U62.16, U63.16, U64.14, U65.1, U65.20, U66.20, U67.16, U68.16, U69.14, U70.20, U71.14, U72.7, U72.9, U72.10, U72.16, U73.31, U73.32, U74.3, U74.31, U74.32, U75.2, U75.31, U75.32, U76.2, U76.3, U76.31, U76.32, U77.6, U77.16, U78.6, U78.16, U79.6, U79.16, U80.1, U80.20, U81.20

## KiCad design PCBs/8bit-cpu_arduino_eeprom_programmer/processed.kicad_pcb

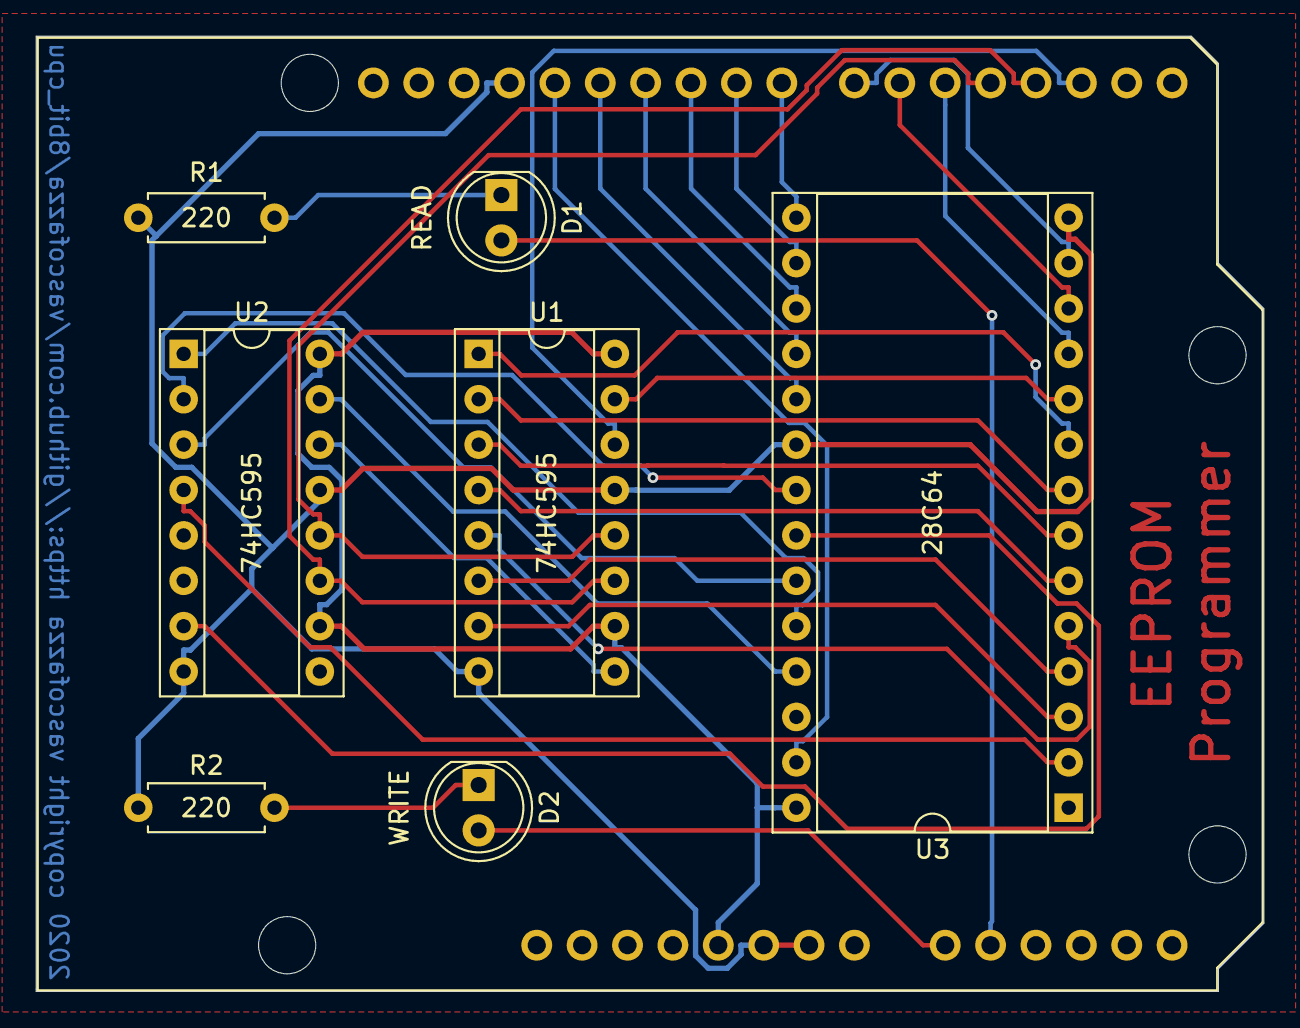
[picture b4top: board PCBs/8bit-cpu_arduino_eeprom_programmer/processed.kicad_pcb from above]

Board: 2 copper layers, 68.7 x 53.5 mm, 8 parts (0 on the bottom side), 33 nets.

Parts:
D1: READ; LED_D5.0mm
D2: WRITE; LED_D5.0mm
R1, R2: 220; R_Axial_DIN0207_L6.3mm_D2.5mm_P7.62mm_Horizontal
U1, U2: 74HC595; DIP-16_W7.62mm_Socket
U3: 28C64; DIP-28_W15.24mm_Socket
XA1: Arduino_Uno_Shield

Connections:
GND: R1.1, R2.1, U1.8, U1.13, U2.8, U2.13, U3.14, U3.20, XA1.GND1, XA1.GND2, XA1.GND3
unnamed: D1.1, R1.2
unnamed: D1.2, XA1.A1
unnamed: D2.1, R2.2
unnamed: D2.2, XA1.A0
unnamed: U1.1, U3.9
unnamed: U1.2, U3.8
unnamed: U1.3, U3.7
unnamed: U1.4, U3.6
unnamed: U1.5, U3.5
unnamed: U1.6, U3.4
unnamed: U1.7, U3.3
unnamed: U1.9, U2.14
unnamed: U1.11, U2.11, XA1.D3
unnamed: U1.12, U2.12, XA1.D4
unnamed: U1.14, XA1.D2
unnamed: U1.15, U3.10
unnamed: U2.1, U3.24
unnamed: U2.2, U3.21
unnamed: U2.3, U3.23
unnamed: U2.4, U3.2
unnamed: U2.7, U3.22
unnamed: U2.15, U3.25
unnamed: U3.11, XA1.D5
unnamed: U3.12, XA1.D6
unnamed: U3.13, XA1.D7
unnamed: U3.15, XA1.D8
unnamed: U3.16, XA1.D9
unnamed: U3.17, XA1.D10
unnamed: U3.18, XA1.D11
unnamed: U3.19, XA1.D12
unnamed: U3.27, XA1.D13
VCC: U1.10, U1.16, U2.10, U2.16, U3.28, XA1.5V1

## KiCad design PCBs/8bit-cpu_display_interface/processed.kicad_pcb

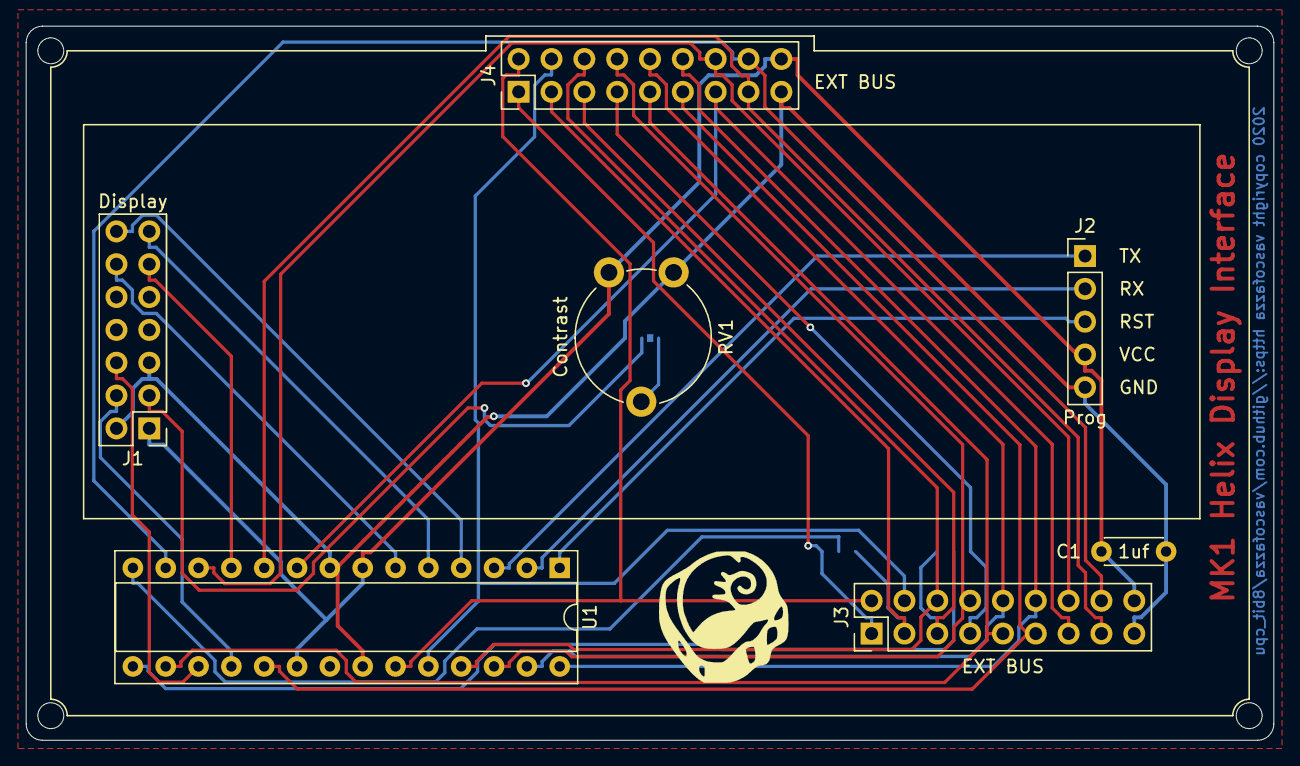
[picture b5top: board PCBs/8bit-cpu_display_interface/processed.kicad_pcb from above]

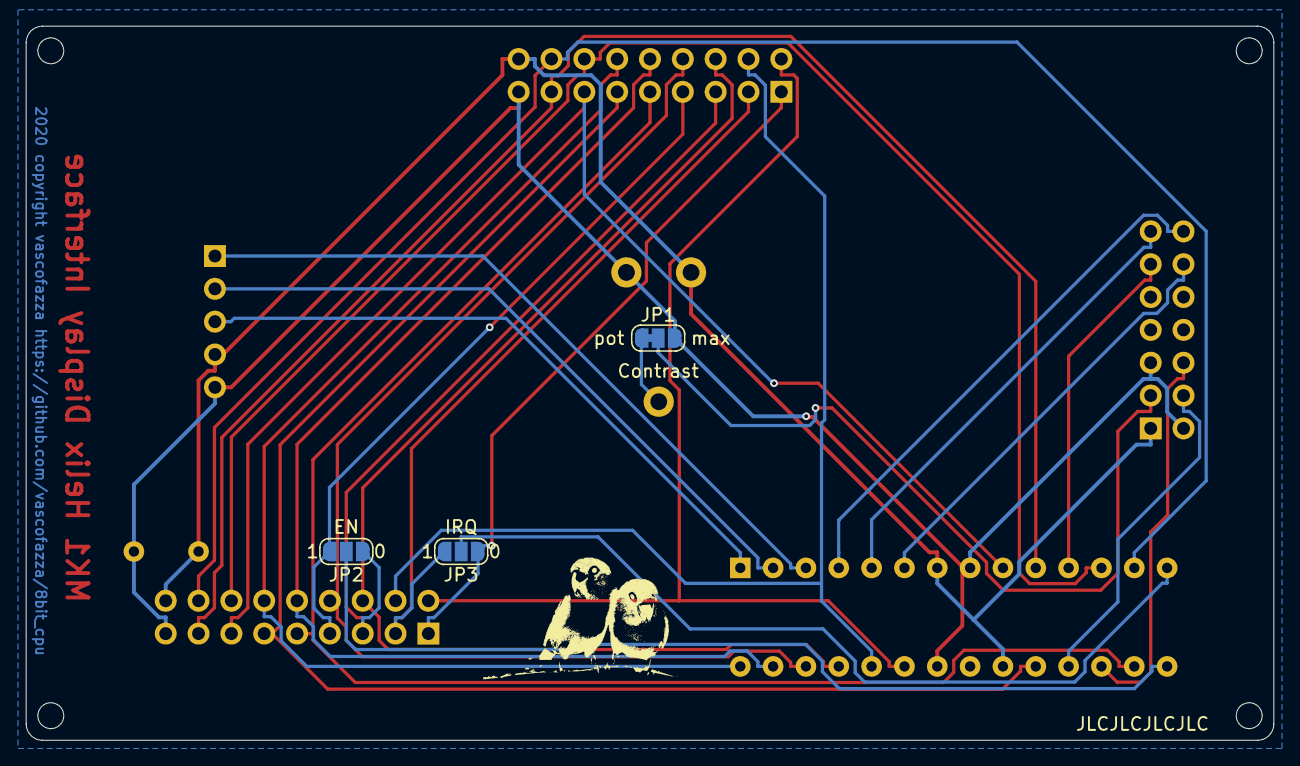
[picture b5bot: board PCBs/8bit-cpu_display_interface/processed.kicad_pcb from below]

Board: 2 copper layers, 96.5 x 55.2 mm, 16 parts (4 on the bottom side), 31 nets.

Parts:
C1: 1uf; C_Disc_D4.3mm_W1.9mm_P5.00mm
J1: Display; PinHeader_2x07_P2.54mm_Vertical
J2: Prog; PinHeader_1x05_P2.54mm_Vertical
J3, J4: EXT BUS; PinHeader_2x09_P2.54mm_Vertical
JP1: Contrast; SolderJumper-3_P1.3mm_Bridged12_RoundedPad1.0x1.5mm_NumberL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
JP2: EN; SolderJumper-3_P1.3mm_Open_RoundedPad1.0x1.5mm_NumberLabels
JP3: IRQ; SolderJumper-3_P1.3mm_Open_RoundedPad1.0x1.5mm_NumberLabels
M0, M1, M2, M3: MountingHole_2mm
RV1: Contrast; Potentiometer_Piher_PT-10-V10_Vertical
S0: LOGO; parrot
S1: LOGO; helix_small
U1: ATmega328-PU; DIP-28_W7.62mm_Socket

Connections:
GND: C1.2, J1.2, J1.5, J2.5, J3.17, J4.17, JP1.3, RV1.3, U1.8, U1.22
unnamed: J1.3, JP1.2
unnamed: J1.4, U1.18
unnamed: J1.6, U1.17
unnamed: J1.11, U1.11
unnamed: J1.12, U1.6
unnamed: J1.13, U1.5
unnamed: J1.14, U1.4
unnamed: J2.1, U1.3
unnamed: J2.2, U1.2
unnamed: J2.3, U1.1
unnamed: J3.1, J4.1, JP3.1
unnamed: J3.2, J4.2, U1.23
unnamed: J3.3, J4.3, JP3.3
unnamed: J3.4, J4.4, U1.24
unnamed: J3.5, J4.5, JP2.1
unnamed: J3.6, J4.6, U1.25
unnamed: J3.7, J4.7, JP2.3
unnamed: J3.8, J4.8, U1.26
unnamed: J3.9, J4.9, U1.16
unnamed: J3.10, J4.10, U1.27
unnamed: J3.11, J4.11, U1.19
unnamed: J3.12, J4.12, U1.28
unnamed: J3.13, J4.13, U1.9
unnamed: J3.14, J4.14, U1.12
unnamed: J3.15, J4.15, U1.10
unnamed: J3.16, J4.16, U1.13
unnamed: JP1.1, RV1.2
unnamed: JP2.2, U1.15
unnamed: JP3.2, U1.14
VCC: C1.1, J1.1, J2.4, J3.18, J4.18, RV1.1, U1.7, U1.20
